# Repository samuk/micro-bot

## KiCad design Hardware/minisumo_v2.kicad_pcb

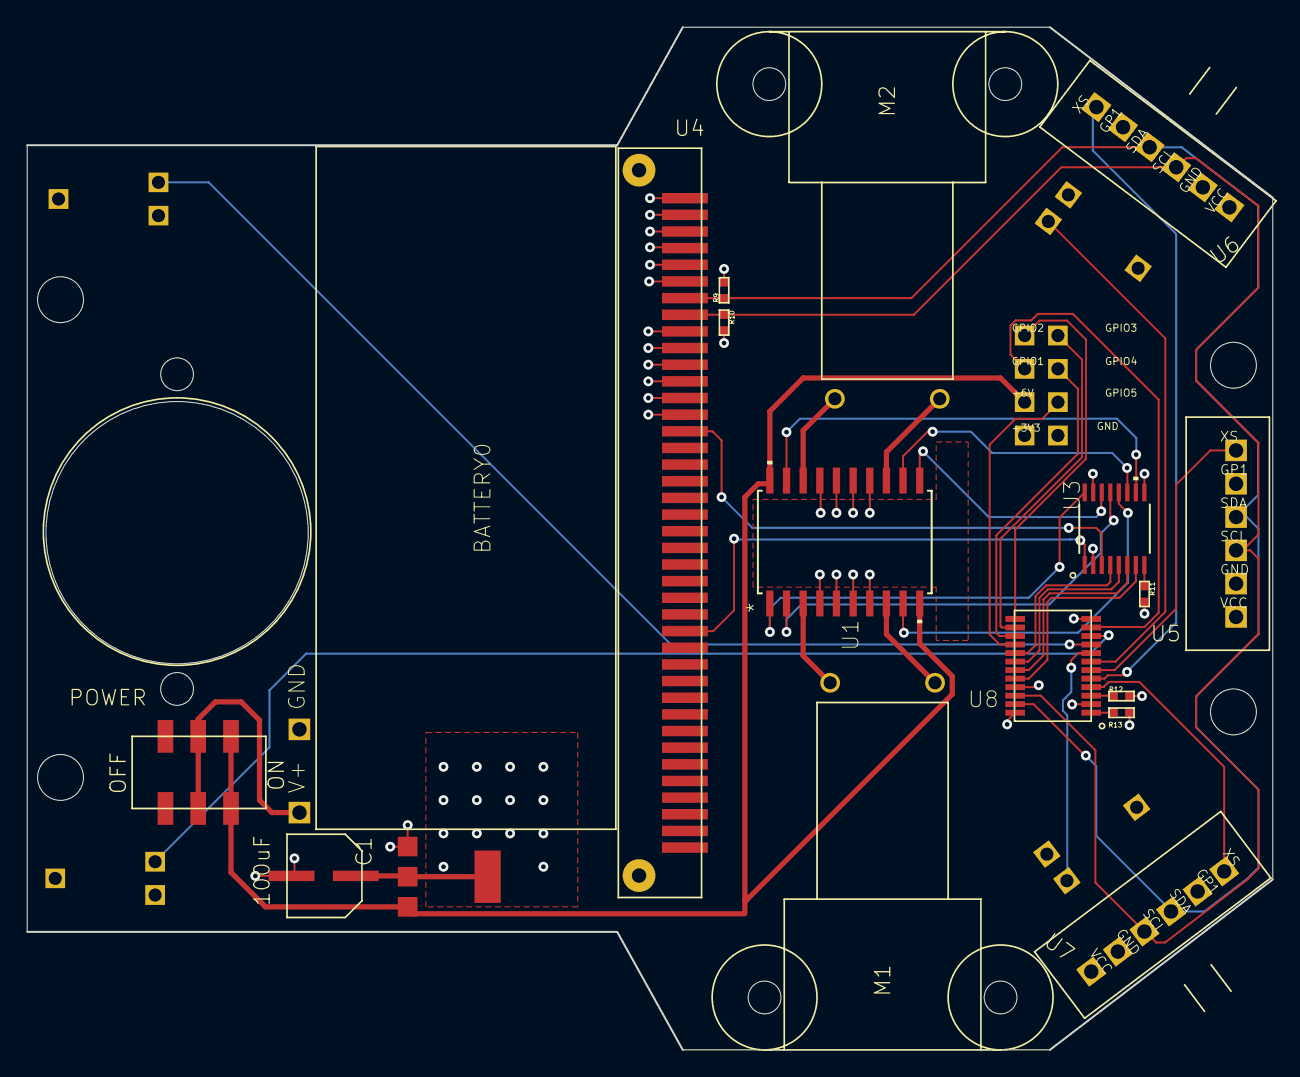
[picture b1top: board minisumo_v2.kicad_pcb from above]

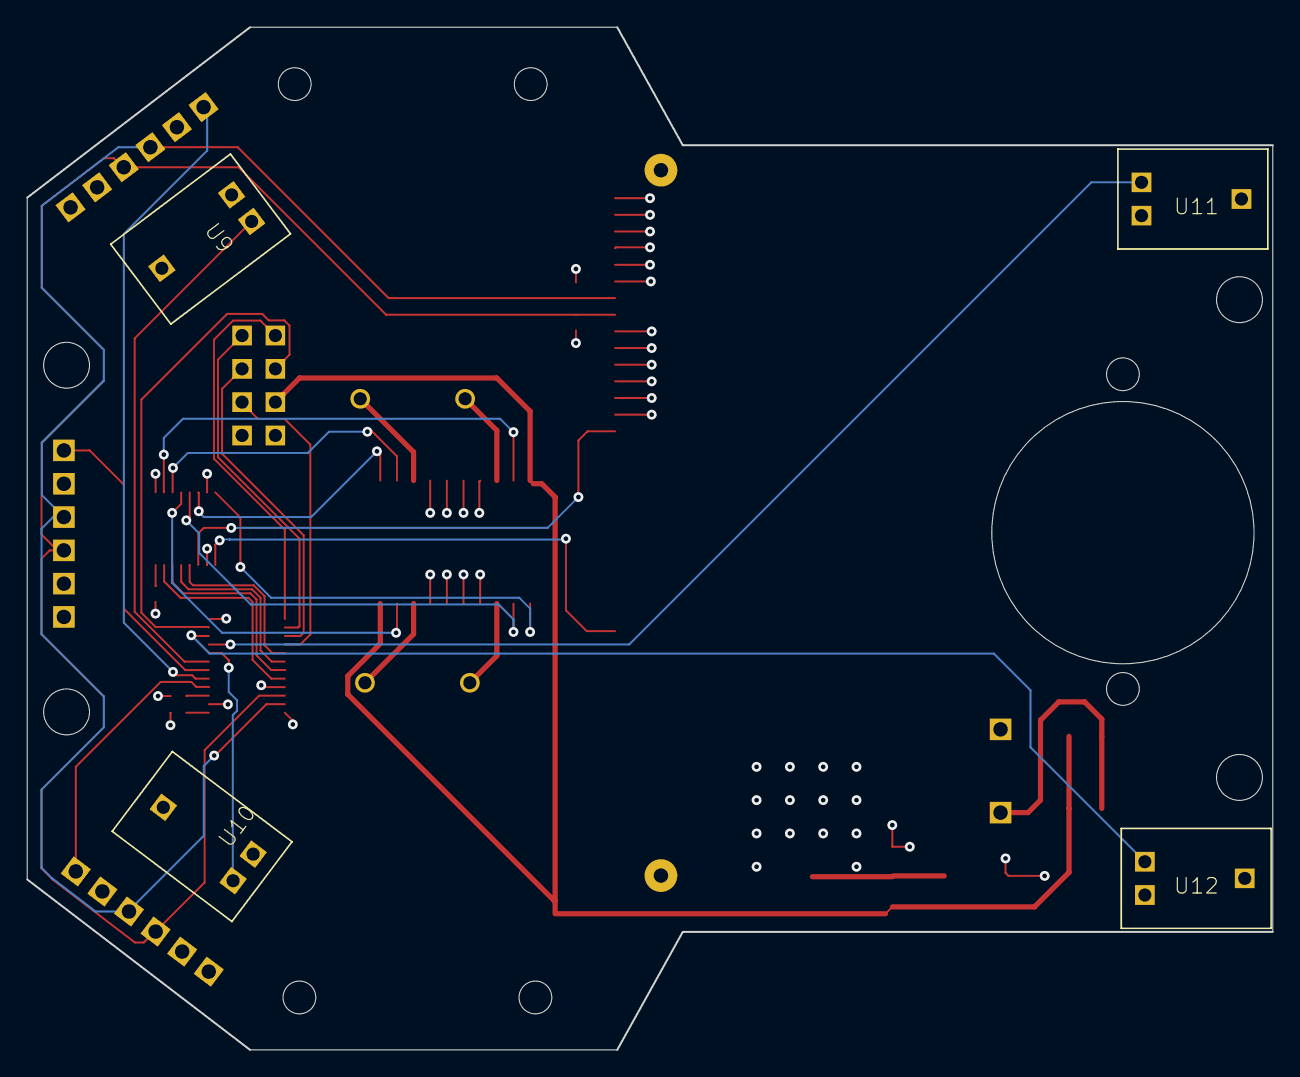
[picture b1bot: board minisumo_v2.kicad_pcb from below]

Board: 4 copper layers, 95.0 x 78.0 mm, 28 parts (4 on the bottom side), 37 nets.

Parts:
@HOLE0, @HOLE1, @HOLE2, @HOLE3: (no value)
BATTERY0: BATTERY_HOLDER_AAA_2X2
C1: 100uF; ALUMINUM_WURTH_100UF_865080243007
M1, M2: N20_MOTOR; N20-MOTOR-BRACKET
R9, R10, R11, R12, R13: 10k; RES_0402
S1: POWER; SWITCH_JS202011SCQN
U1: L293DD; SO-20
U2: SOT-223
U3: TXB0106PWRPW16-L; PW16-L
U4: BBC Micro:bit; CYCLONE_MICROBIT_VERTICAL
U5: VL53LOX - Right; VL53LOX
U6: VL53LOX - Center; VL53LOX
U7: VL53LOX - Left; VL53LOX
U8: TCA9539PWR; 24-TSSOP
U9: NW; QRE1113_MODULE
U10: NE; QRE1113_MODULE
U11: SW; QRE1113_MODULE
U12: SE; QRE1113_MODULE
U$1: CASTER
U$3: SUMO_IO

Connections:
+3V3: C1.+, R9.P$2, R10.P$2, R11.P$2, R12.P$2, R13.P$2, U2.P$2, U2.VOUT$1, U3.2, U4.3.3V@9, U4.3.3V@10, U4.3.3V@11, U4.3.3V@12, U4.3.3V@13, U4.3.3V@14, U5.VCC, U6.VCC, U7.VCC, U8.24, U9.+3V3, U10.+3V3, U11.+3V3, U12.+3V3, U$3.3V3
+5V: S1.3, S1.6, U1.10, U1.20, U2.VIN, U3.15, U$3.6V
GND: BATTERY0.-, C1.-, U1.4, U1.5, U1.6, U1.7, U1.14, U1.15, U1.16, U1.17, U2.GND, U3.9, U4.GND@1, U4.GND@2, U4.GND@3, U4.GND@4, U4.GND@5, U4.GND@6, U5.GND, U6.GND, U7.GND, U8.2, U8.12, U8.21, U9.GND, U10.GND, U11.GND, U12.GND, U$3.GND
INPUT_1: U3.4, U8.17
INPUT_2: U3.5, U8.18
INPUT_3: U3.6, U8.19
INPUT_4: U3.7, U8.20
IO1: U8.11, U$3.GPIO1
IO2: U8.13, U$3.GPIO2
IO3: U8.14, U$3.GPIO3
IO4: U8.15, U$3.GPIO4
IO5: U8.16, U$3.GPIO5
unnamed: U1.1, U3.16
unnamed: U1.11, U3.14
unnamed: U1.2, U3.13
unnamed: U1.9, U3.12
unnamed: M1.1, U1.3
unnamed: M1.2, U1.8
unnamed: M2.1, U1.13
unnamed: M2.2, U1.18
unnamed: U3.1, U4.P8
unnamed: U1.12, U3.11
unnamed: U3.3, U4.P16
unnamed: U1.19, U3.10
unnamed: BATTERY0.+, S1.2, S1.5
unnamed: R11.P$1, U3.8
unnamed: R12.P$1, U8.3
unnamed: R13.P$1, U8.1
NE: U8.8, U10.SIGNAL
NW: U8.7, U9.SIGNAL
SCL: R10.P$1, U4.P21_SCL, U5.SCL, U6.SCL, U7.SCL, U8.22
SDA: R9.P$1, U4.P20_SDA, U5.SDA, U6.SDA, U7.SDA, U8.23
SE: U8.10, U12.SIGNAL
SW: U8.9, U11.SIGNAL
XS1: U7.XSHUT, U8.4
XS2: U6.XSHUT, U8.5
XS3: U5.XSHUT, U8.6

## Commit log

2022-09-07 Kicad 6 versions
